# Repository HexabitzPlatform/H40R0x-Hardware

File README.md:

# H40R0x-Hardware
Hexabitz STLINK-V3MODS Programmer Module Hardware Design

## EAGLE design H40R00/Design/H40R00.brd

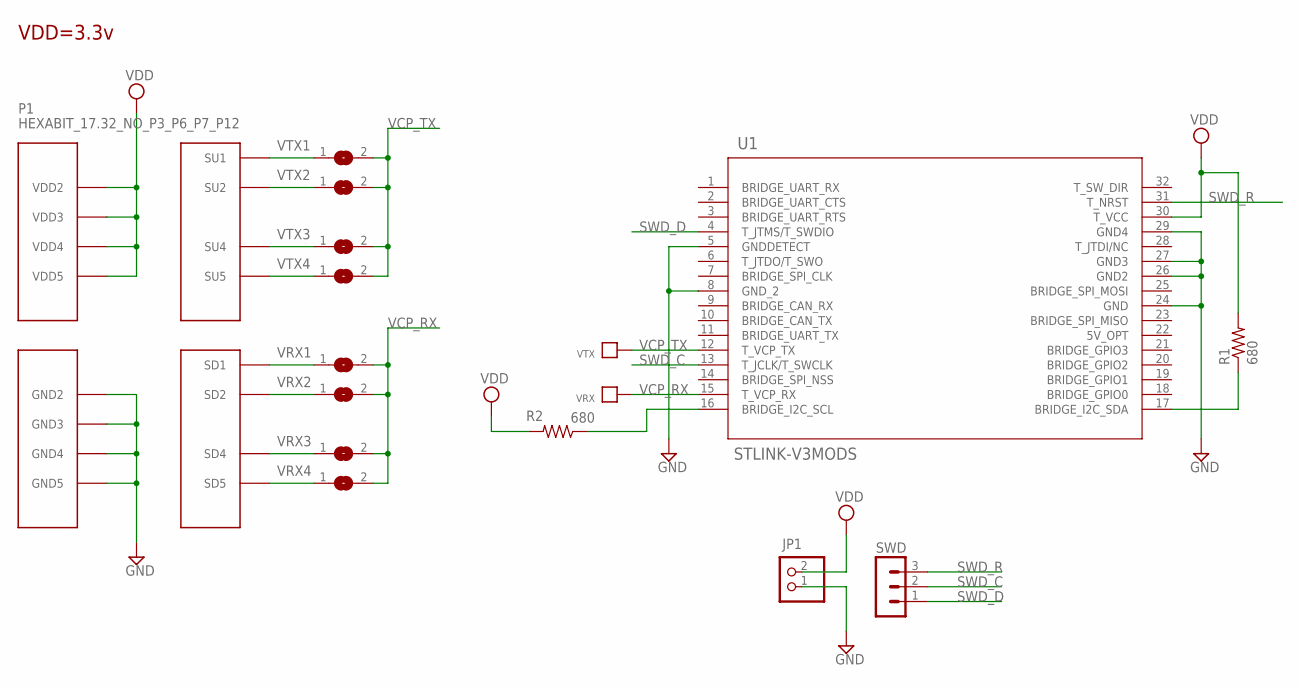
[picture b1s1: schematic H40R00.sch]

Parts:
JP1: PINHD-1X2; 1X02
P1: HEXABIT_17.32_NO_P3_P6_P7_P12
R1, R2: 680; R-0603; TOLERANCE 5%; MPN RC0603JR-07680RL
SWD: MA03-1
U1: STLINK-V3MODS; MOD_STLINK-V3M_MB1467
VRX: PAD4
VRX1, VRX2, VRX3, VRX4: SJ
VTX: PAD4
VTX1, VTX2, VTX3, VTX4: SJ

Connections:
GND: JP1.1, P1.PAD_PD8 (GND2), P1.PAD_PD9 (GND3), P1.PAD_PD10 (GND4), P1.PAD_PD11 (GND5), U1.5 (GNDDETECT), U1.8 (GND_2), U1.24 (GND), U1.26 (GND2), U1.27 (GND3), U1.29 (GND4)
unnamed: R2.1, U1.16 (BRIDGE_I2C_SCL)
unnamed: R1.1, U1.17 (BRIDGE_I2C_SDA)
SWD_C: SWD.2, U1.13 (T_JCLK/T_SWCLK)
SWD_D: SWD.1, U1.4 (T_JTMS/T_SWDIO)
SWD_R: SWD.3, U1.31 (T_NRST)
UART2_RX: P1.PAD_PD1 (SD1), VRX1.1
UART2_TX: P1.PAD_PU1 (SU1), VTX1.1
UART3_RX: P1.PAD_PD4 (SD4), VRX3.1
UART3_TX: P1.PAD_PU4 (SU4), VTX3.1
UART4_RX: P1.PAD_PD5 (SD5), VRX4.1
UART4_TX: P1.PAD_PU5 (SU5), VTX4.1
UART6_RX: P1.PAD_PD2 (SD2), VRX2.1
UART6_TX: P1.PAD_PU2 (SU2), VTX2.1
VCP_RX: U1.15 (T_VCP_RX), VRX.P$1, VRX1.2, VRX2.2, VRX3.2, VRX4.2
VCP_TX: U1.12 (T_VCP_TX), VTX.P$1, VTX1.2, VTX2.2, VTX3.2, VTX4.2
VDD: JP1.2, P1.PAD_PU8 (VDD2), P1.PAD_PU9 (VDD3), P1.PAD_PU10 (VDD4), P1.PAD_PU11 (VDD5), R1.2, R2.2, U1.30 (T_VCC)

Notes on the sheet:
VDD=3.3v

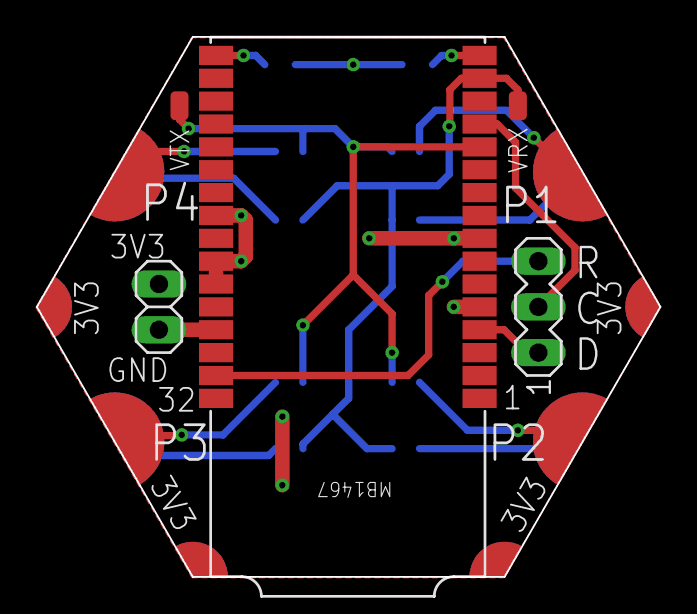
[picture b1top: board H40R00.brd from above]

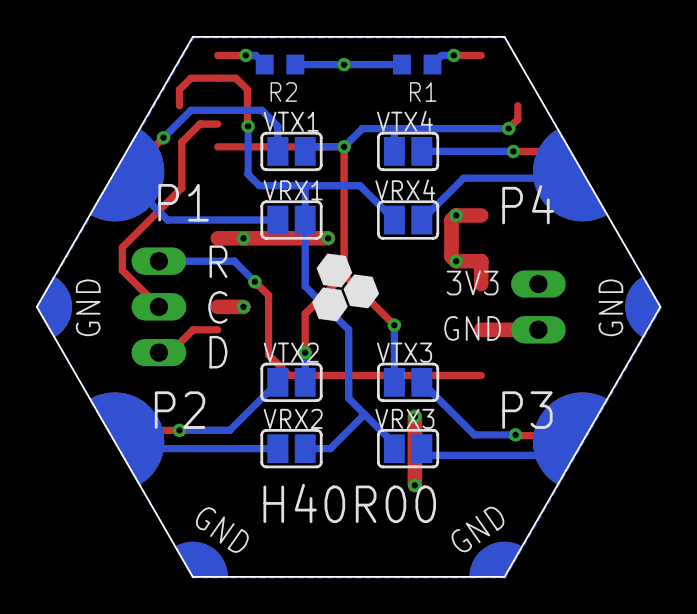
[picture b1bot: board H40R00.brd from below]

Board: 2 copper layers, 34.6 x 30.0 mm, 16 parts (10 on the bottom side), 17 nets.

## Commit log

2020-05-17 Finished schematics
2020-05-21 Finished placement and routing
2020-05-21 Generate output files Release V0
